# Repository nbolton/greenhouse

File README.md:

# Greenhouse
## An attempt to automate nature 🌶

### Prerequesits
- VSCode with Platform.io extension
- MinGW if Windows
  - [Chocolatey](https://chocolatey.org/): `choco install mingw`
  - Alternative: [MinGW](https://sourceforge.net/projects/mingwbuilds/files/latest/download)

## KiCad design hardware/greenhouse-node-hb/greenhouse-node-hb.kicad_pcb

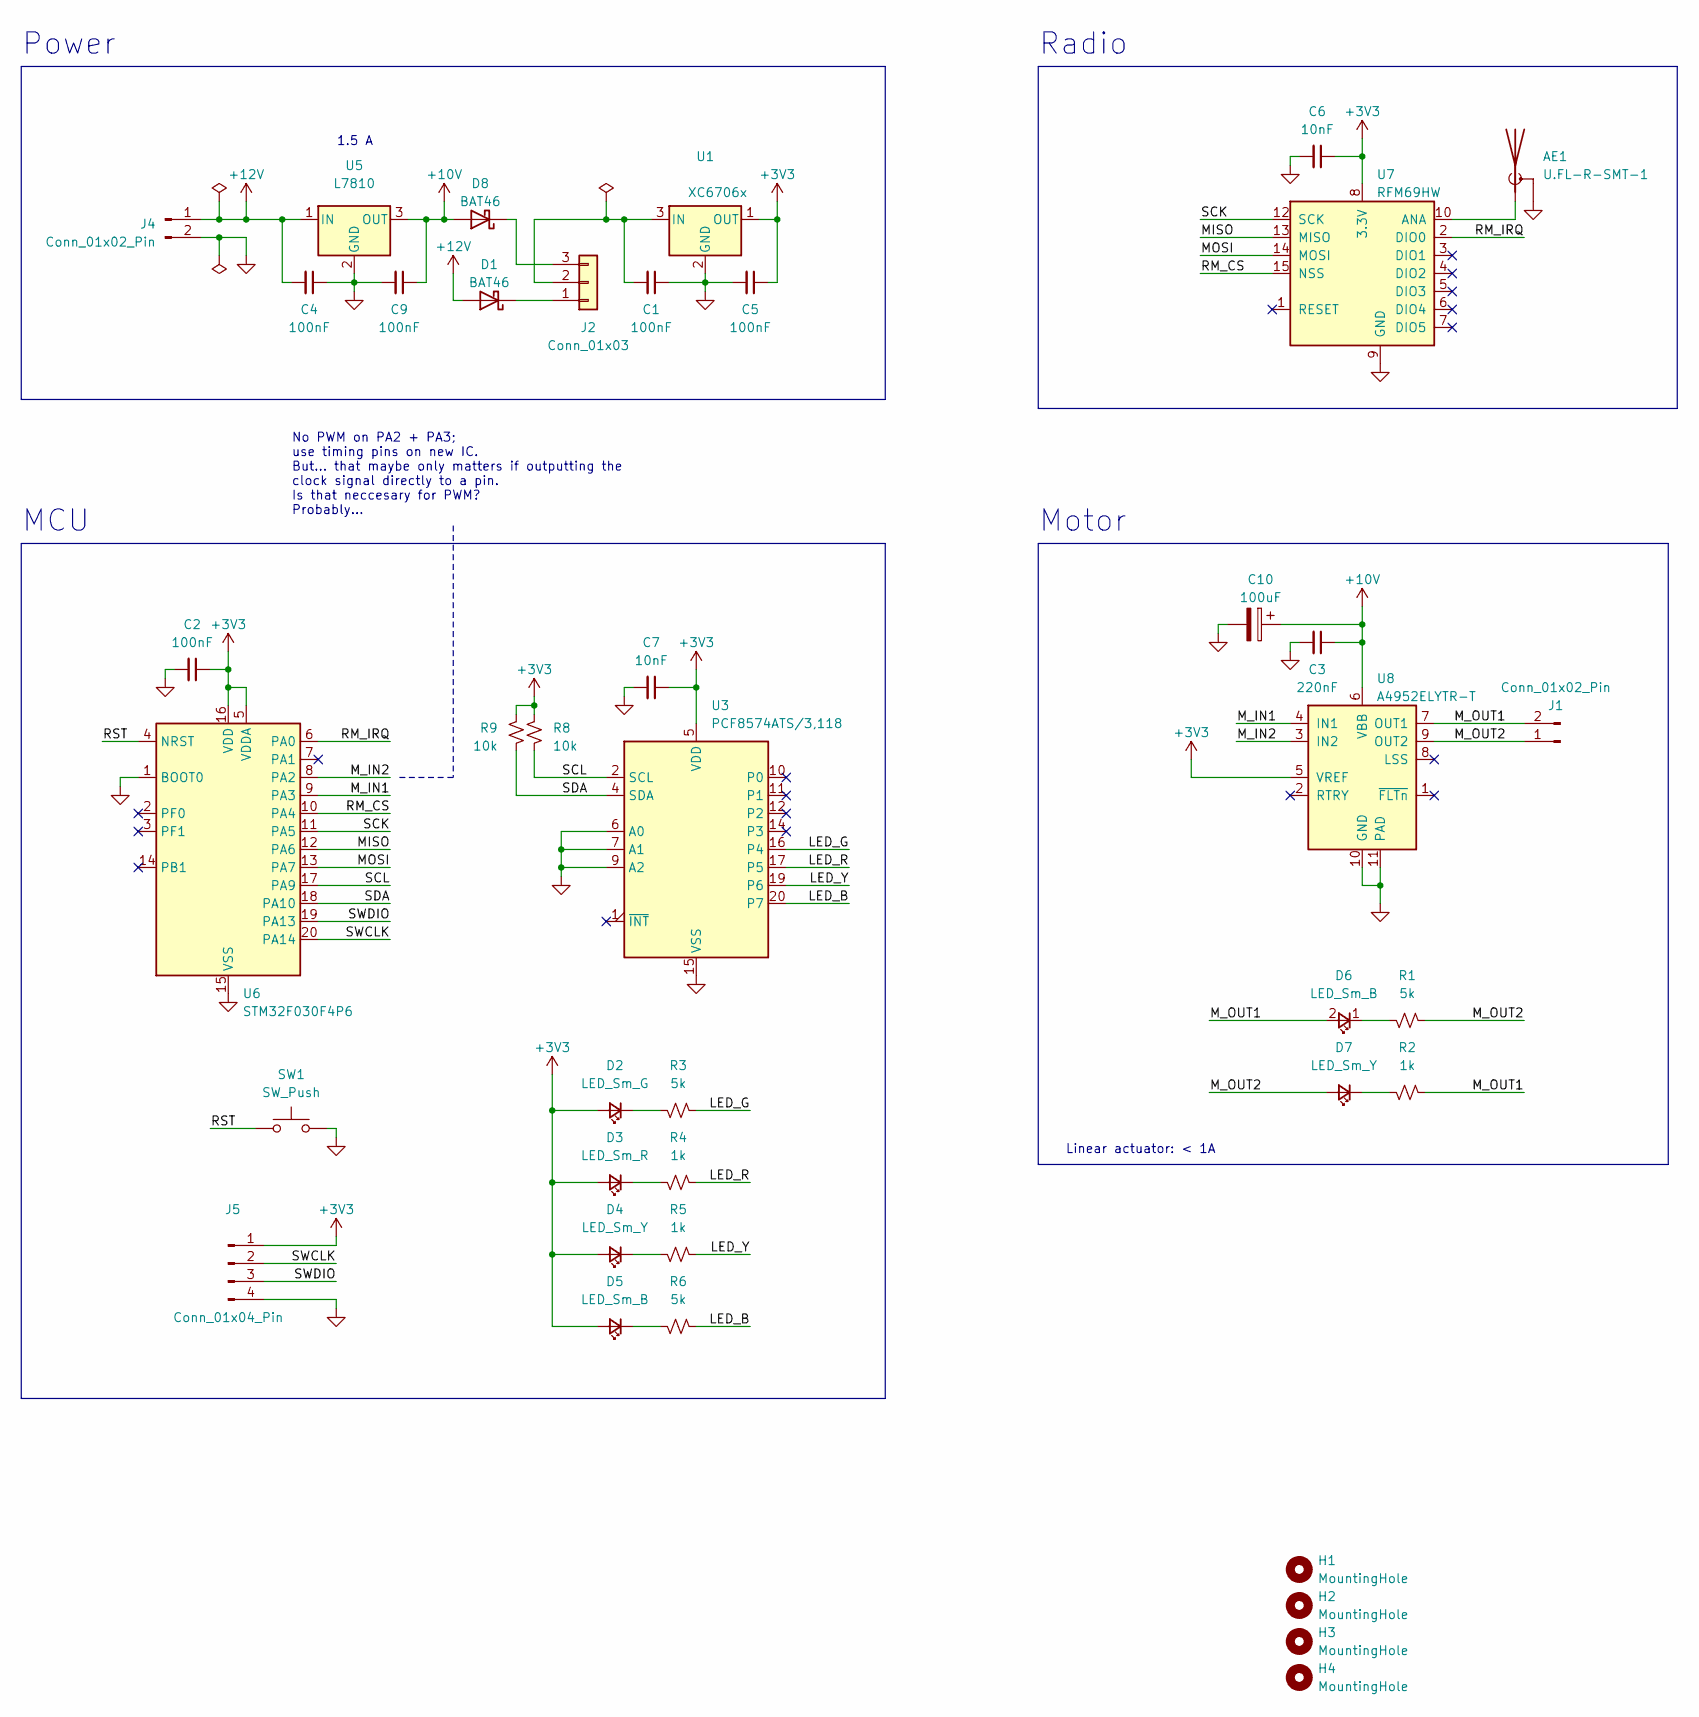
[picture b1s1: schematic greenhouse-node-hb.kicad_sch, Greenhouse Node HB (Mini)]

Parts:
AE1: U.FL-R-SMT-1; U.FL_Hirose_U.FL-R-SMT-1_Vertical
C1, C2, C4, C5, C9: 100nF; C_Disc_D4.7mm_W2.5mm_P5.00mm
C3: 220nF; C_Disc_D4.7mm_W2.5mm_P5.00mm
C6, C7: 10nF; C_Disc_D3.0mm_W2.0mm_P2.50mm
C10: 100uF; CP_Radial_D6.3mm_P2.50mm
D1, D8: BAT46; D_DO-35_SOD27_P7.62mm_Horizontal
D2: LED_Sm_G; LED_D3.0mm
D3: LED_Sm_R; LED_D3.0mm
D4, D7: LED_Sm_Y; LED_D3.0mm
D5, D6: LED_Sm_B; LED_D3.0mm
H1, H2, H3, H4: MountingHole; MountingHole_3.2mm_M3
J1, J4: Conn_01x02_Pin; Molex_KK-254_AE-6410-02A_1x02_P2.54mm_Vertical
J2: Conn_01x03; SolderJumper-3_P1.3mm_Bridged2Bar12_RoundedPad1.0x1.5mm
J5: Conn_01x04_Pin; JST_PH_B4B-PH-K_1x04_P2.00mm_Vertical
R1, R3, R6: 5k; R_Axial_DIN0207_L6.3mm_D2.5mm_P7.62mm_Horizontal
R2, R4, R5: 1k; R_Axial_DIN0207_L6.3mm_D2.5mm_P7.62mm_Horizontal
R8, R9: 10k; R_Axial_DIN0207_L6.3mm_D2.5mm_P7.62mm_Horizontal
SW1: SW_Push; SW_PUSH_6mm
U1: XC6706x; SOT-89-3
U3: PCF8574ATS/3,118; SSOP-20_4.4x6.5mm_P0.65mm
U5: L7810; TO-220-3_Horizontal_TabUp
U6: STM32F030F4P6; TSSOP-20_4.4x6.5mm_P0.65mm
U7: RFM69HW; HopeRF_RFM69HW
U8: A4952ELYTR-T; MSOP-10-1EP_3x3mm_P0.5mm_EP1.73x1.98mm

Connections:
+3V3: C2.1, C5.1, C6.1, C7.1, D2.2 (A), D3.2 (A), D4.2 (A), D5.2 (A), J5.1, R8.1, R9.1, U1.1 (OUT), U3.5 (VDD), U6.5 (VDDA), U6.16 (VDD), U7.8 (3.3V), U8.5 (VREF)
+10V: C3.1, C9.1, C10.1, D8.2 (A), U5.3 (OUT), U8.6 (VBB)
+12V: C4.2, D1.2 (A), J4.1, U5.1 (IN)
/LED_B: R6.1, U3.20 (P7)
/LED_G: R3.1, U3.16 (P4)
/LED_R: R4.1, U3.17 (P5)
/LED_Y: R5.1, U3.19 (P6)
/MISO: U6.12 (PA6), U7.13 (MISO)
/MOSI: U6.13 (PA7), U7.14 (MOSI)
/M_IN1: U6.9 (PA3), U8.4 (IN1)
/M_IN2: U6.8 (PA2), U8.3 (IN2)
/M_OUT1: D6.2 (A), J1.2, R2.1, U8.7 (OUT1)
/M_OUT2: D7.2 (A), J1.1, R1.1, U8.9 (OUT2)
/RM_CS: U6.10 (PA4), U7.15 (NSS)
/RM_IRQ: U6.6 (PA0), U7.2 (DIO0)
/RST: SW1.1, U6.4 (NRST)
/SCK: U6.11 (PA5), U7.12 (SCK)
/SCL: R8.2, U3.2 (SCL), U6.17 (PA9)
/SDA: R9.2, U3.4 (SDA), U6.18 (PA10)
/SWCLK: J5.2, U6.20 (PA14)
/SWDIO: J5.3, U6.19 (PA13)
GND: AE1.2 (Shield), C1.1, C2.2, C3.2, C4.1, C5.2, C6.2, C7.2, C9.2, C10.2, J4.2, J5.4, SW1.2, U1.2 (GND), U3.6 (A0), U3.7 (A1), U3.9 (A2), U3.15 (VSS), U5.2 (GND), U6.1 (BOOT0), U6.15 (VSS), U7.9 (GND), U7.11 (GND), U8.10 (GND), U8.11 (PAD)
unnamed: C1.2, J2.2, U1.3 (IN)
unnamed: AE1.1 (A), U7.10 (ANA)
unnamed: D1.1 (K), J2.1
unnamed: D2.1 (K), R3.2
unnamed: D3.1 (K), R4.2
unnamed: D4.1 (K), R5.2
unnamed: D5.1 (K), R6.2
unnamed: D6.1 (K), R1.2
unnamed: D7.1 (K), R2.2
unnamed: D8.1 (K), J2.3

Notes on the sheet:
Motor
MCU
Linear actuator: < 1A
Power
No PWM on PA2 + PA3; use timing pins on new IC. But... that maybe only matters if outputting the clock signal directly to a pin. Is that neccesary for PWM? Probably...
1.5 A
Radio

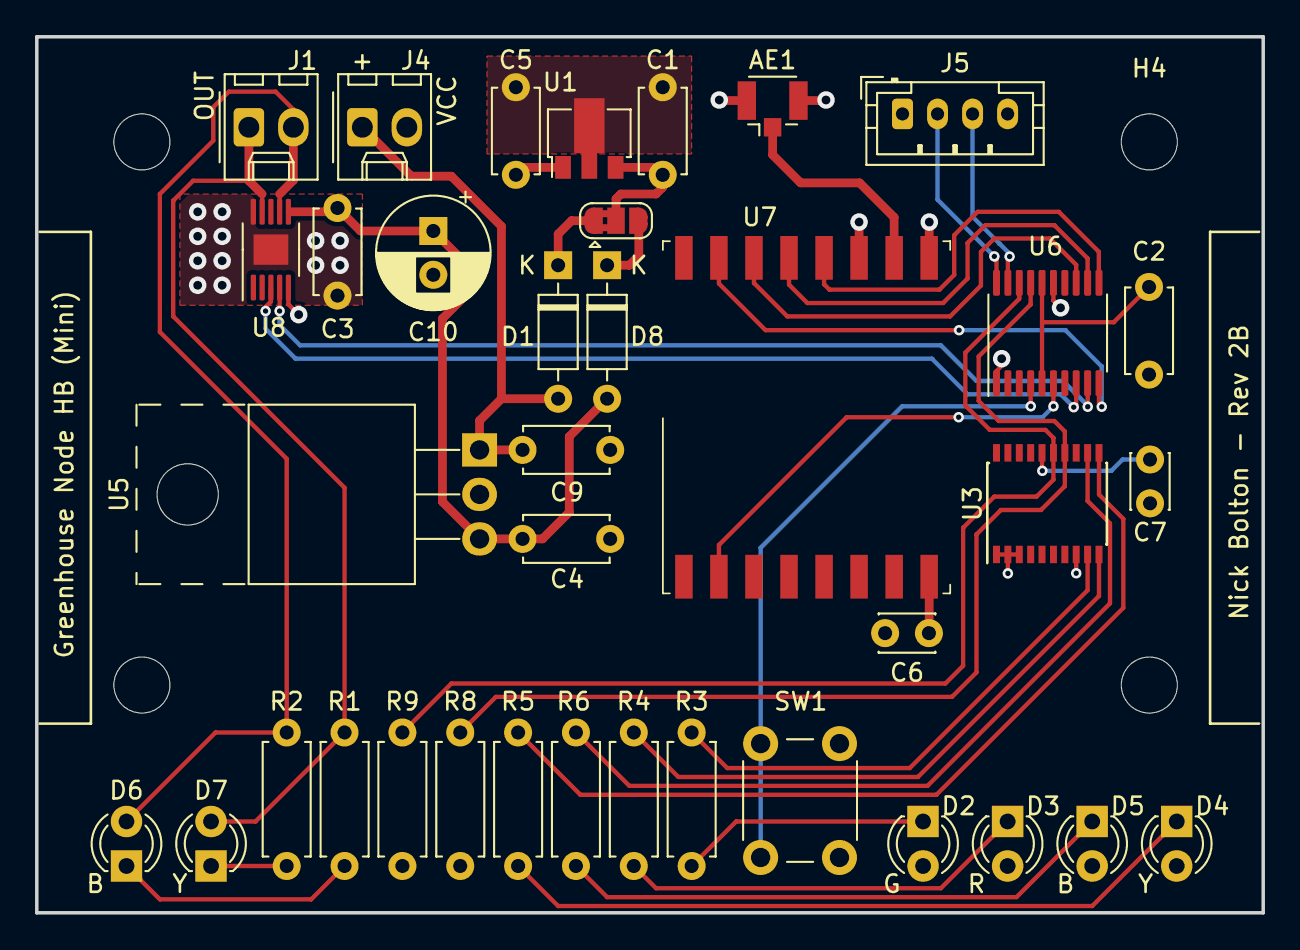
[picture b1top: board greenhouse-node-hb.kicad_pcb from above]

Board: 4 copper layers, 70.0 x 50.0 mm, 41 parts (0 on the bottom side), 32 nets.

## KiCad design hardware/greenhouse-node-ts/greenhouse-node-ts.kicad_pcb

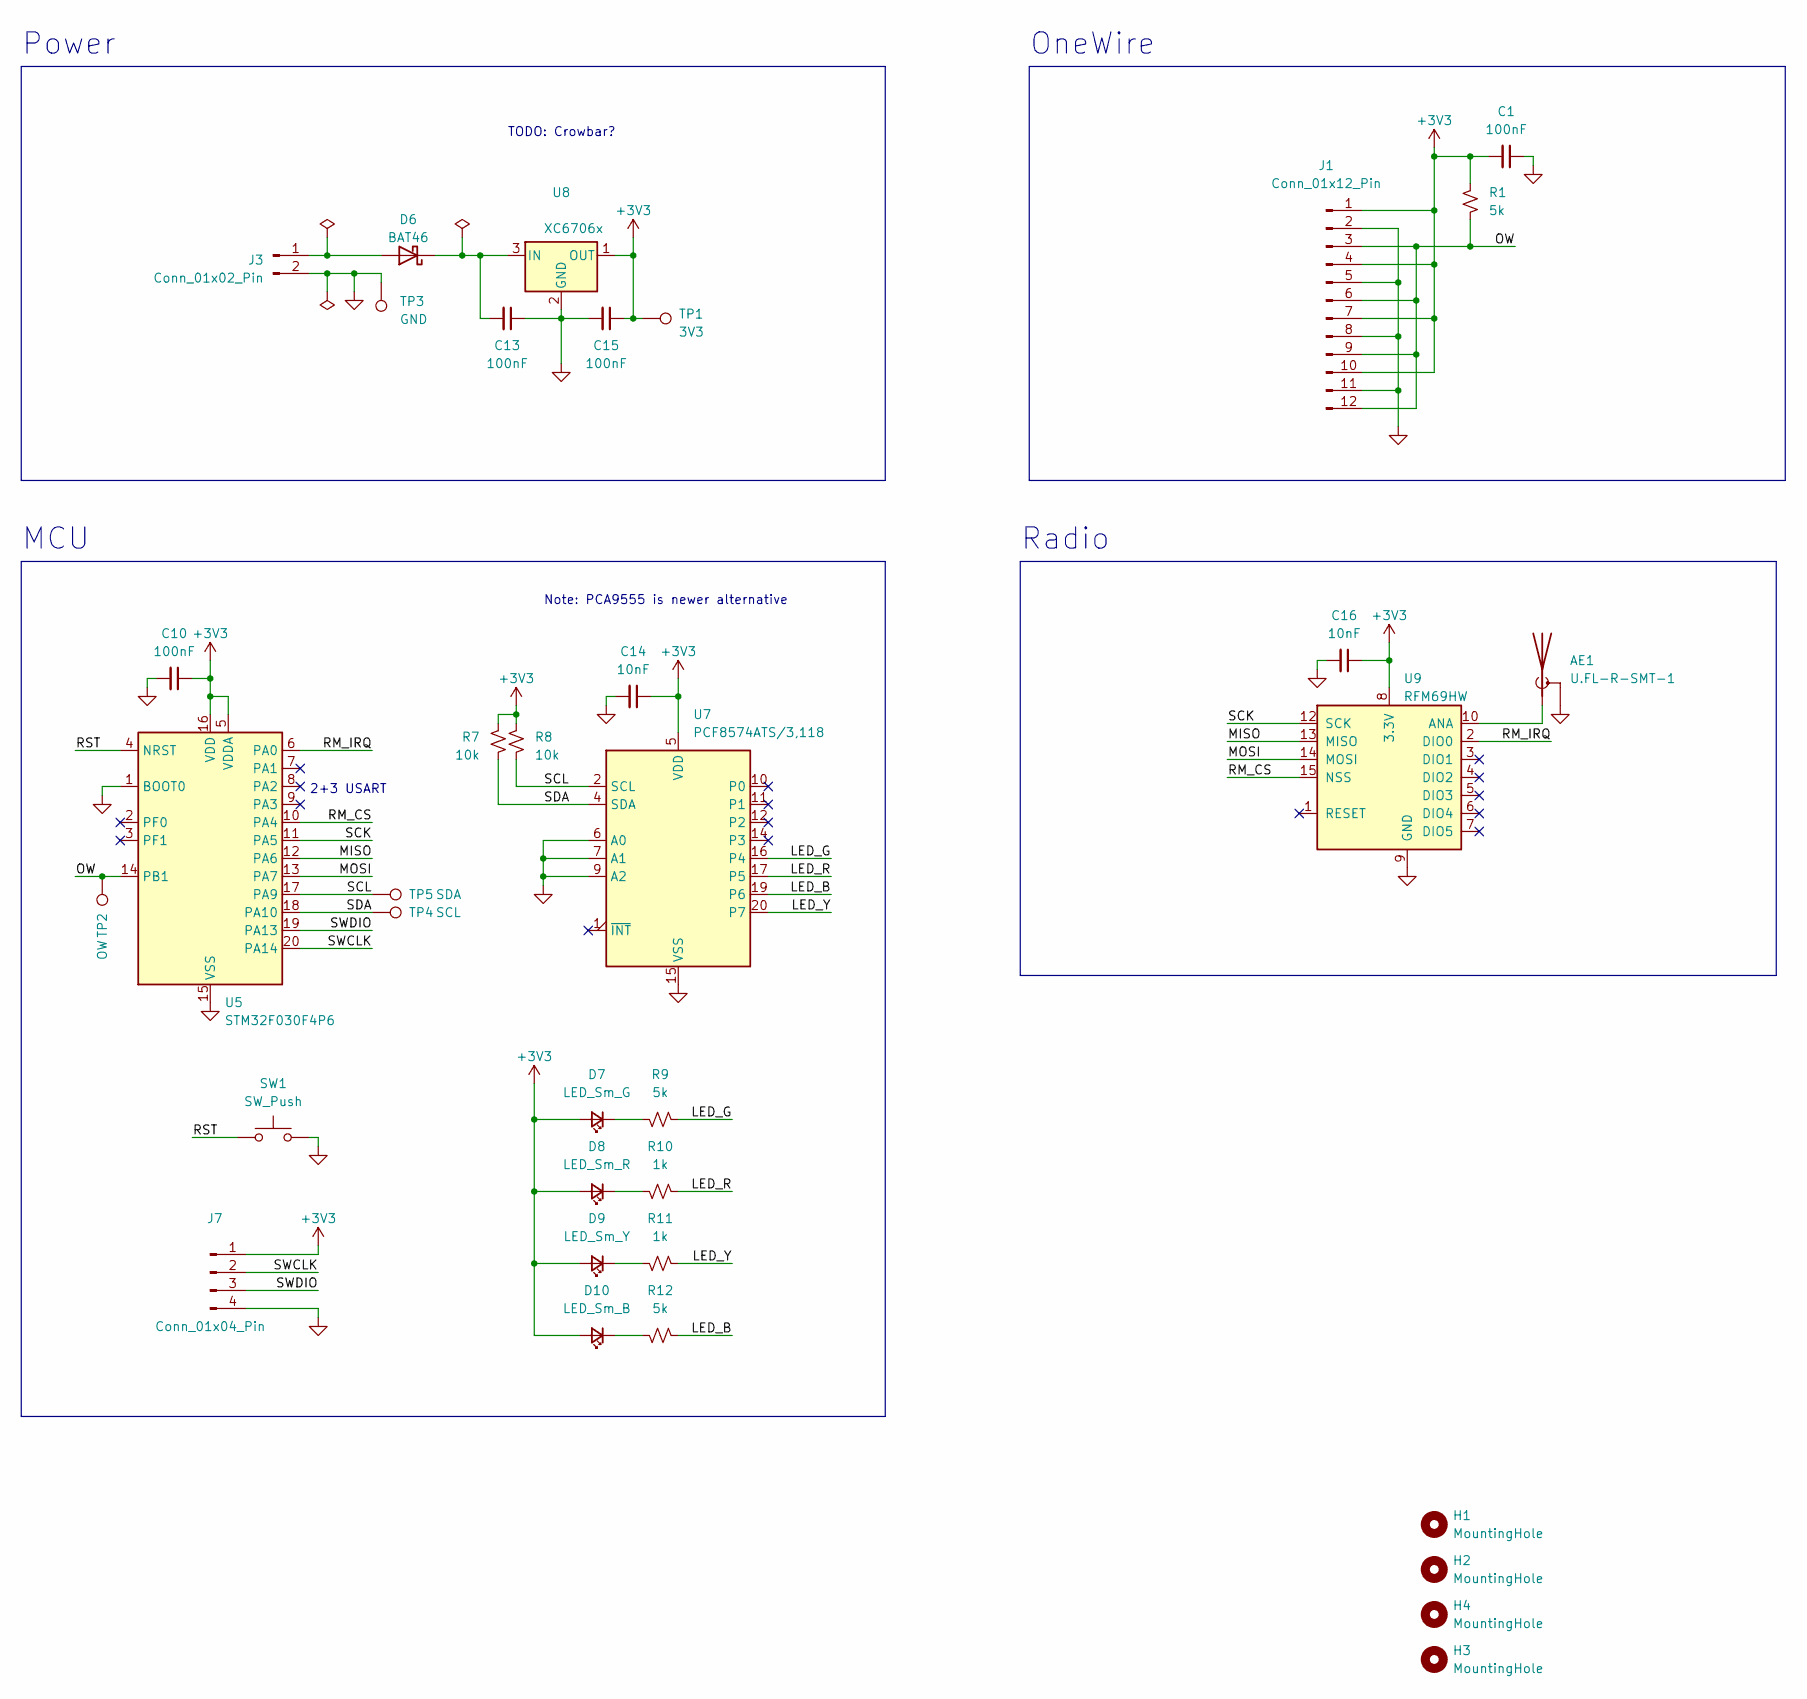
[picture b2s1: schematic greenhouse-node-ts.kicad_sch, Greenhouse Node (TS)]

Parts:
AE1: U.FL-R-SMT-1; U.FL_Hirose_U.FL-R-SMT-1_Vertical
C1, C10, C13, C15: 100nF; C_Disc_D4.7mm_W2.5mm_P5.00mm
C14, C16: 10nF; C_Disc_D3.0mm_W2.0mm_P2.50mm
D6: BAT46; D_DO-35_SOD27_P7.62mm_Horizontal
D7: LED_Sm_G; LED_D3.0mm
D8: LED_Sm_R; LED_D3.0mm
D9: LED_Sm_Y; LED_D3.0mm
D10: LED_Sm_B; LED_D3.0mm
H1, H2, H3, H4: MountingHole; MountingHole_3.2mm_M3
J1: Conn_01x12_Pin; JST_PH_B12B-PH-K_1x12_P2.00mm_Vertical
J3: Conn_01x02_Pin; Molex_KK-254_AE-6410-02A_1x02_P2.54mm_Vertical
J7: Conn_01x04_Pin; JST_PH_B4B-PH-K_1x04_P2.00mm_Vertical
R1, R9, R12: 5k; R_Axial_DIN0207_L6.3mm_D2.5mm_P7.62mm_Horizontal
R7, R8: 10k; R_Axial_DIN0207_L6.3mm_D2.5mm_P7.62mm_Horizontal
R10, R11: 1k; R_Axial_DIN0207_L6.3mm_D2.5mm_P7.62mm_Horizontal
SW1: SW_Push; SW_PUSH_6mm
TP1: 3V3; TestPoint_Keystone_5019_Minature
TP2: OW; TestPoint_Keystone_5019_Minature
TP3: GND; TestPoint_Keystone_5019_Minature
TP4: SCL; TestPoint_Keystone_5019_Minature
TP5: SDA; TestPoint_Keystone_5019_Minature
U5: STM32F030F4P6; TSSOP-20_4.4x6.5mm_P0.65mm
U7: PCF8574ATS/3,118; SSOP-20_4.4x6.5mm_P0.65mm
U8: XC6706x; SOT-89-3
U9: RFM69HW; HopeRF_RFM69HW

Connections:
+3V3: C1.2, C10.1, C14.1, C15.1, C16.1, D7.2 (A), D8.2 (A), D9.2 (A), D10.2 (A), J1.1, J1.4, J1.7, J1.10, J7.1, R1.1, R7.1, R8.1, TP1.1, U5.5 (VDDA), U5.16 (VDD), U7.5 (VDD), U8.1 (OUT), U9.8 (3.3V)
/LED_B: R12.1, U7.19 (P6)
/LED_G: R9.1, U7.16 (P4)
/LED_R: R10.1, U7.17 (P5)
/LED_Y: R11.1, U7.20 (P7)
/MISO: U5.12 (PA6), U9.13 (MISO)
/MOSI: U5.13 (PA7), U9.14 (MOSI)
/OW: J1.3, J1.6, J1.9, J1.12, R1.2, TP2.1, U5.14 (PB1)
/RM_CS: U5.10 (PA4), U9.15 (NSS)
/RM_IRQ: U5.6 (PA0), U9.2 (DIO0)
/RST: SW1.1, U5.4 (NRST)
/SCK: U5.11 (PA5), U9.12 (SCK)
/SCL: R8.2, TP5.1, U5.17 (PA9), U7.2 (SCL)
/SDA: R7.2, TP4.1, U5.18 (PA10), U7.4 (SDA)
/SWCLK: J7.2, U5.20 (PA14)
/SWDIO: J7.3, U5.19 (PA13)
GND: AE1.2 (Shield), C1.1, C10.2, C13.1, C14.2, C15.2, C16.2, J1.2, J1.5, J1.8, J1.11, J3.2, J7.4, SW1.2, TP3.1, U5.1 (BOOT0), U5.15 (VSS), U7.6 (A0), U7.7 (A1), U7.9 (A2), U7.15 (VSS), U8.2 (GND), U9.9 (GND), U9.11 (GND)
unnamed: AE1.1 (A), U9.10 (ANA)
unnamed: D6.2 (A), J3.1
unnamed: C13.2, D6.1 (K), U8.3 (IN)
unnamed: D7.1 (K), R9.2
unnamed: D8.1 (K), R10.2
unnamed: D9.1 (K), R11.2
unnamed: D10.1 (K), R12.2

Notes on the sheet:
Note: PCA9555 is newer alternative
Power
MCU
OneWire
Radio
TODO: Crowbar?
2+3 USART

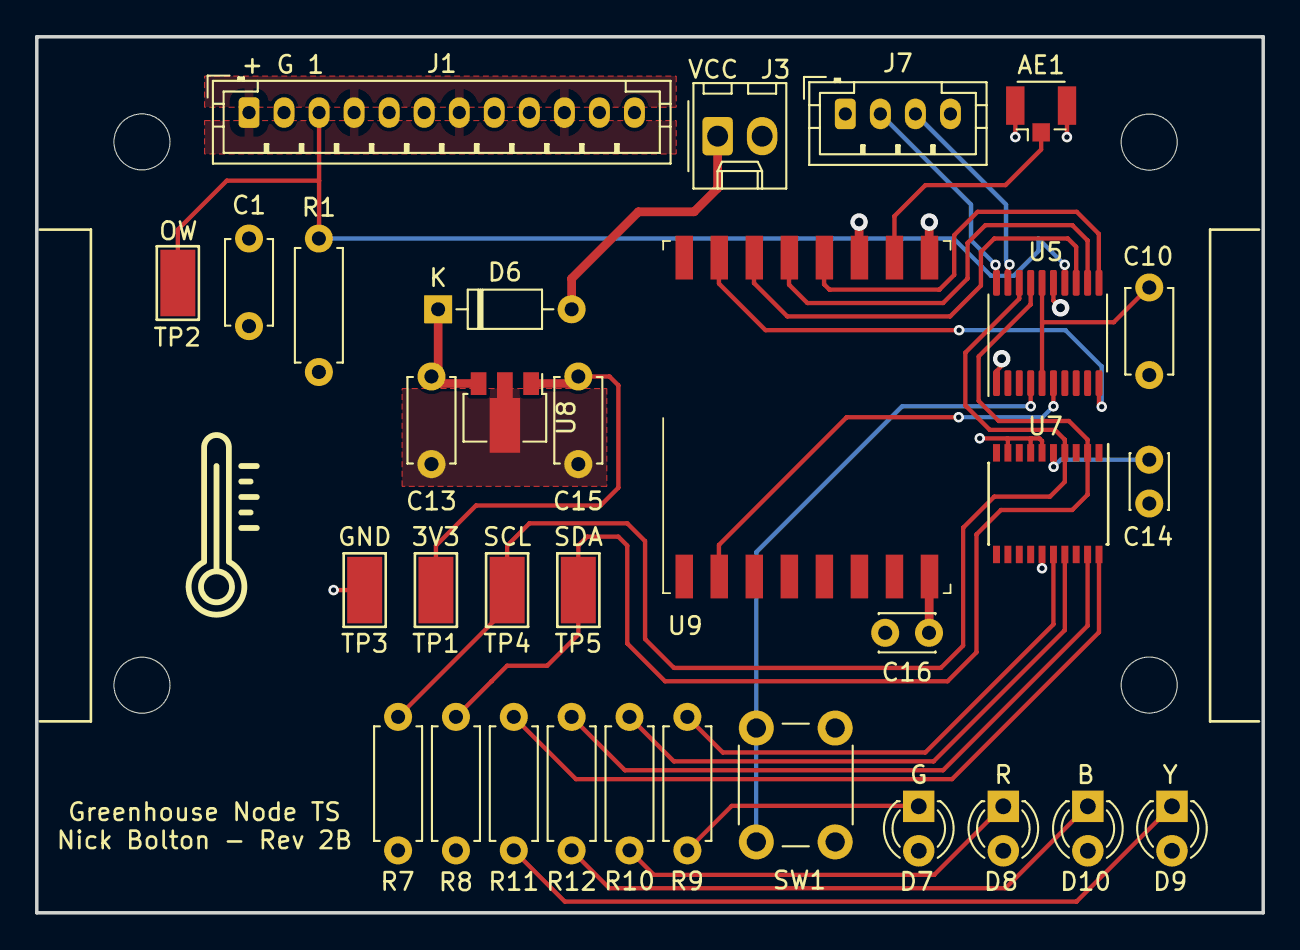
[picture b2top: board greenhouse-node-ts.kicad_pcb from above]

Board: 4 copper layers, 70.0 x 50.0 mm, 36 parts (0 on the bottom side), 24 nets.

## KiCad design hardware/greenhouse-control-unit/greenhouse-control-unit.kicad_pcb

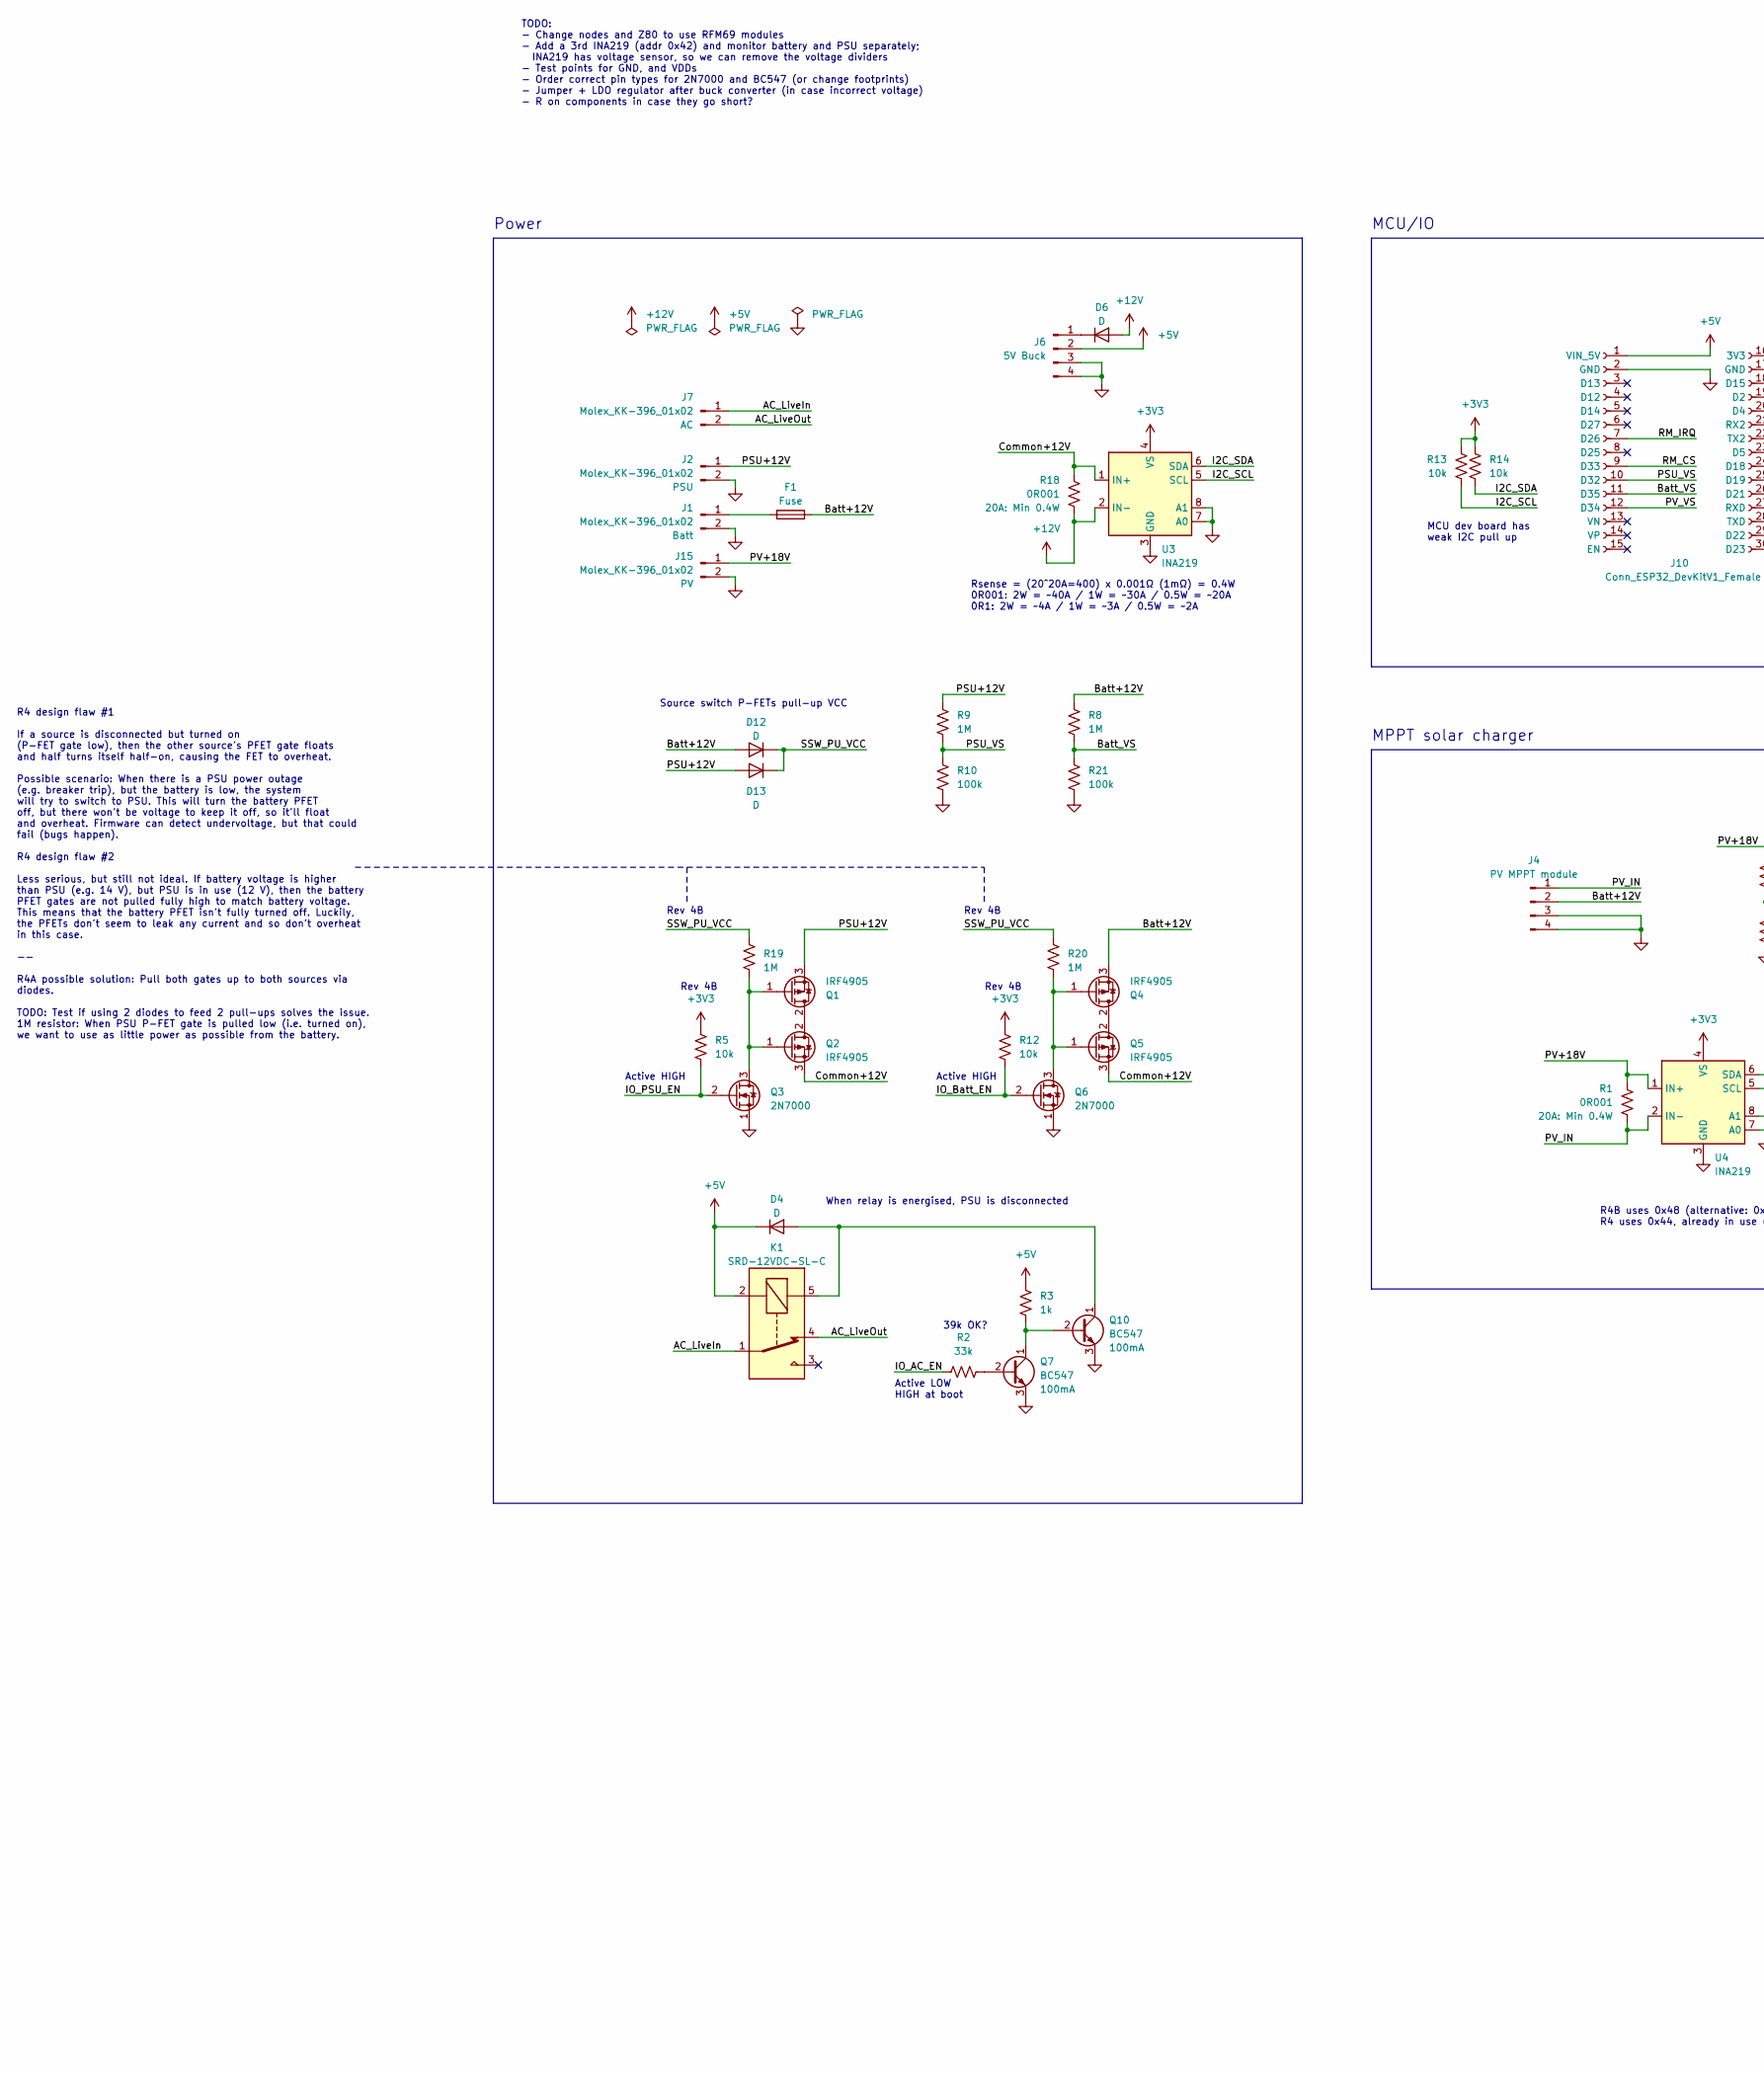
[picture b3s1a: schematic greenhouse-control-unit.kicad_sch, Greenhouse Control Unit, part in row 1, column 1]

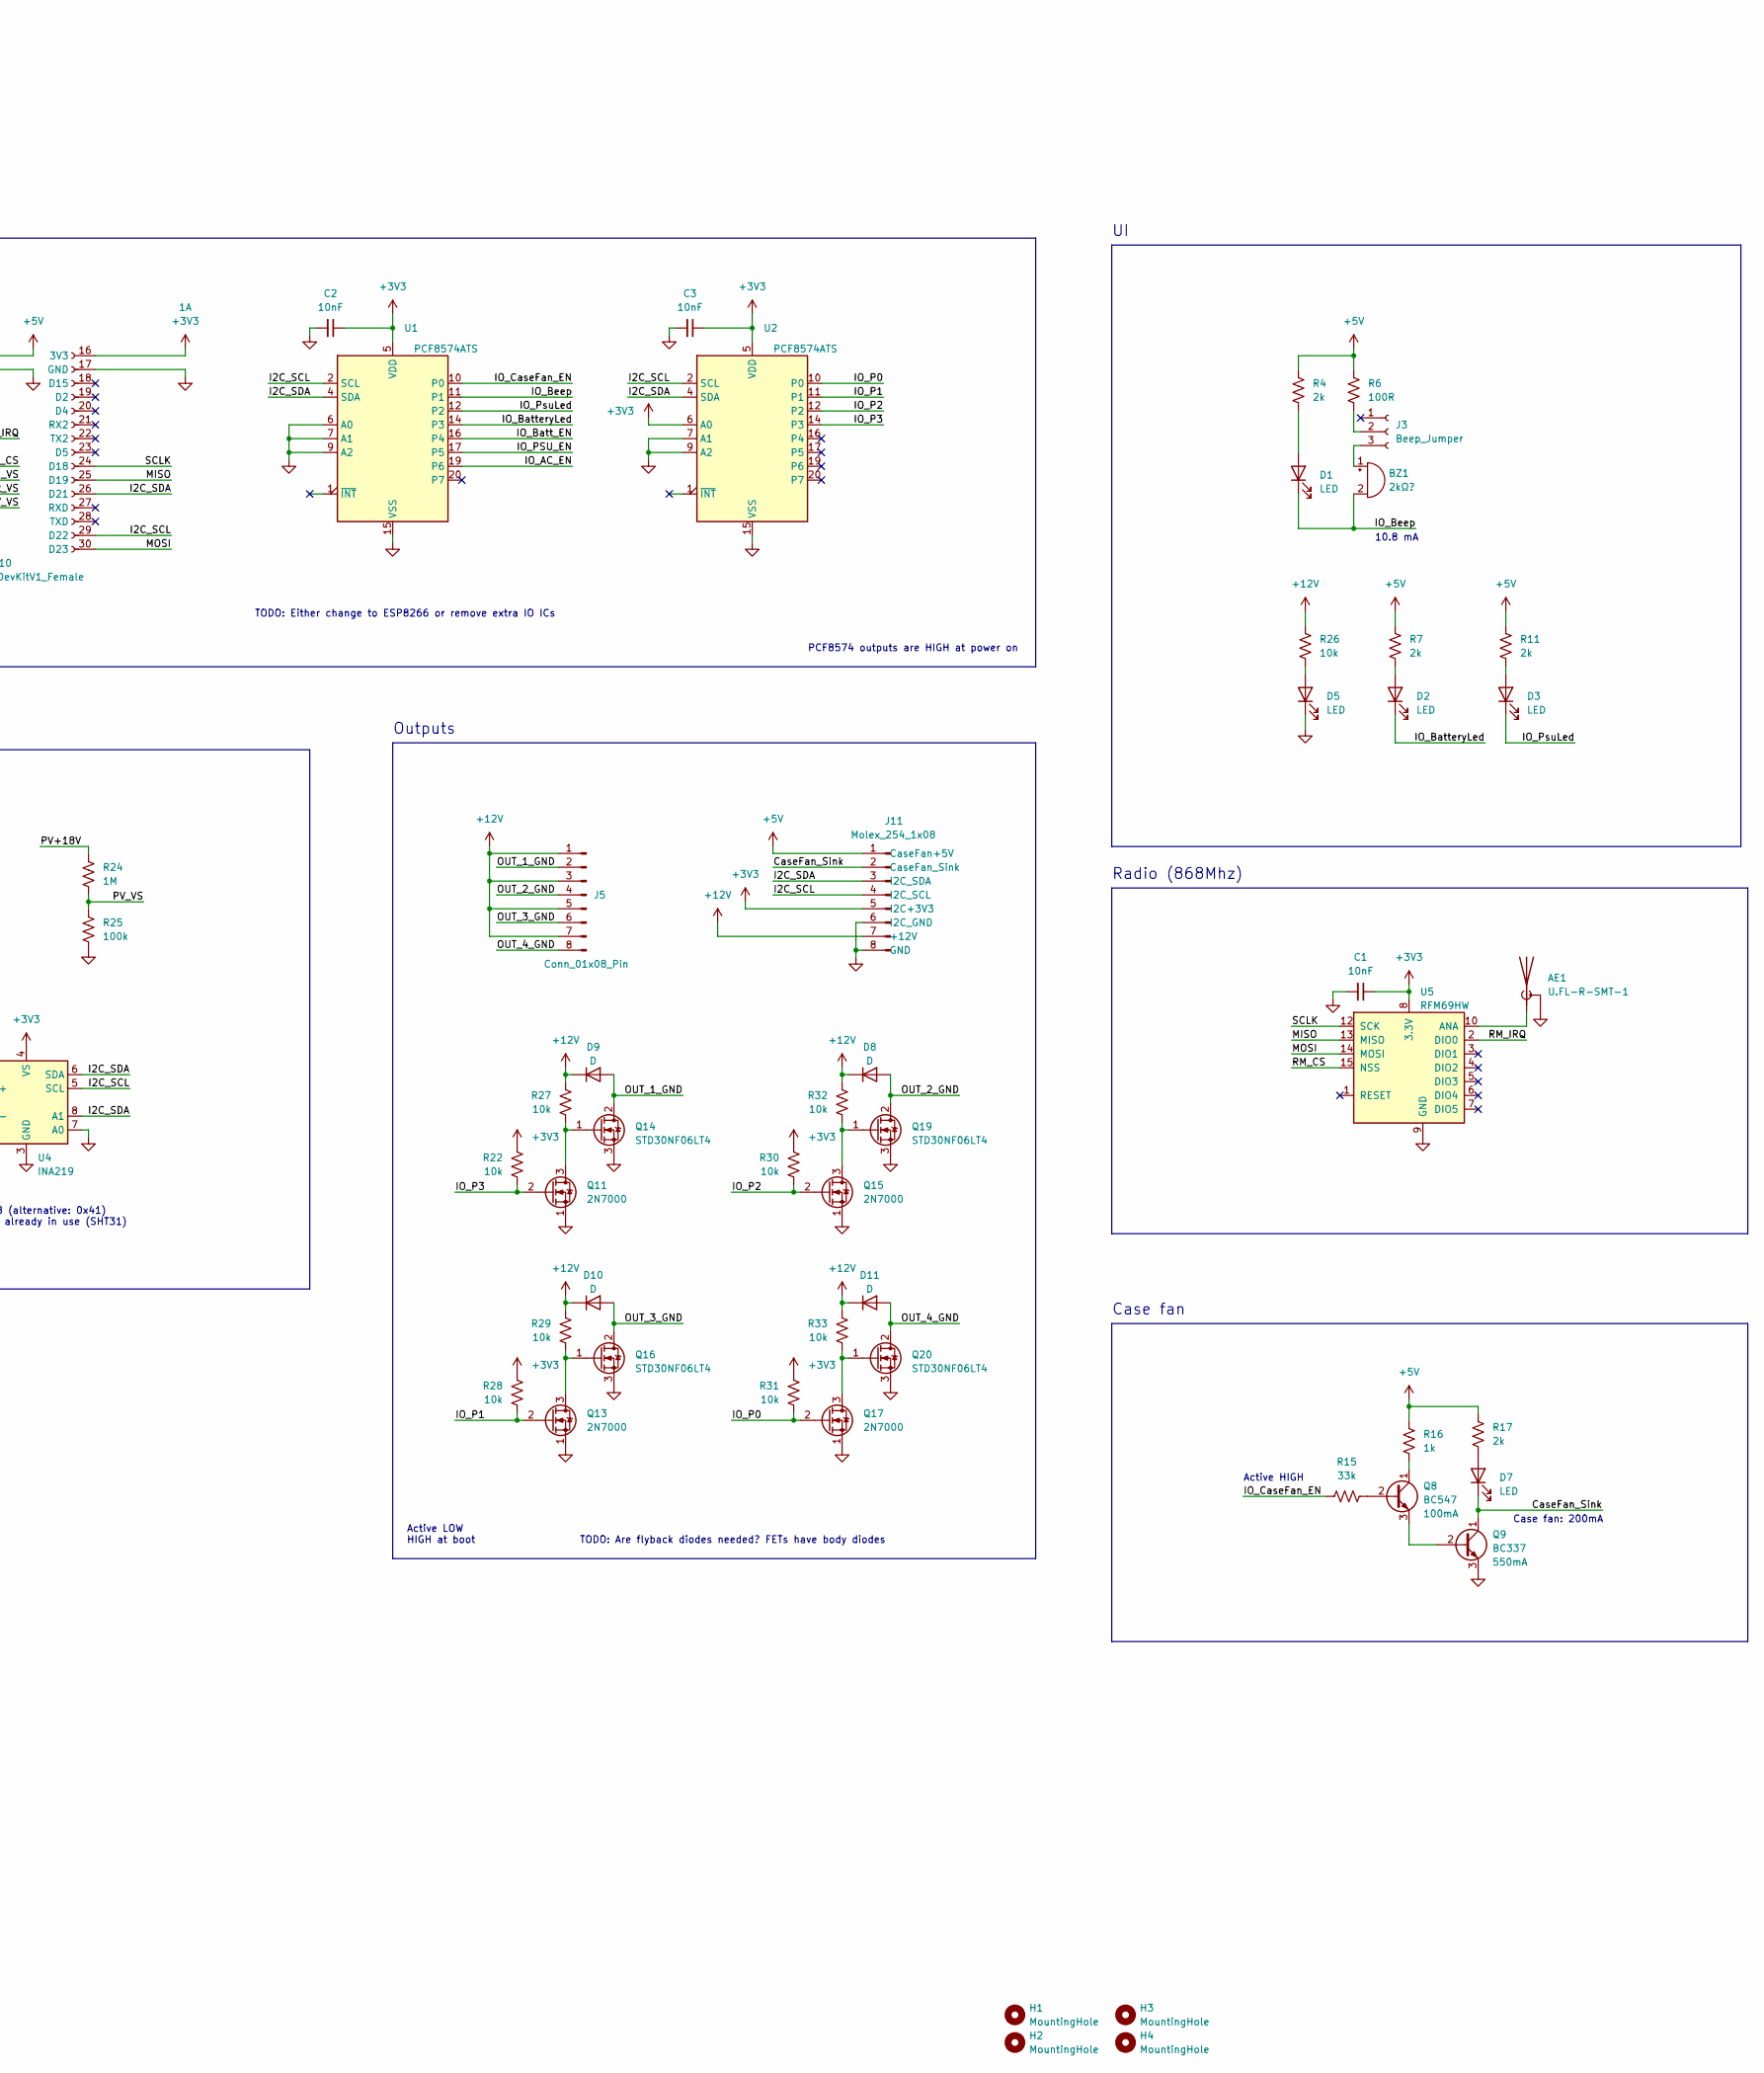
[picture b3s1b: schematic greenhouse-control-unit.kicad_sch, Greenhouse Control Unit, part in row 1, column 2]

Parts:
AE1: U.FL-R-SMT-1; U.FL_Hirose_U.FL-R-SMT-1_Vertical
BZ1: 2kΩ?; Buzzer_12x9.5RM7.6
C1, C2, C3: 10nF; C_Disc_D3.0mm_W2.0mm_P2.50mm
D1, D2, D3, D5, D7: LED; LED_D5.0mm
D4, D12, D13: D; D_DO-35_SOD27_P7.62mm_Horizontal
D6: D; D_DO-41_SOD81_P7.62mm_Horizontal
D8, D9, D10, D11: D; D_DO-41_SOD81_P2.54mm_Vertical_AnodeUp
F1: Fuse; Fuse_3522-2_L
H1, H2, H3, H4: MountingHole; MountingHole_3mm
J1, J2, J7, J15: Molex_KK-396_01x02; Molex_KK-396_1x02_P3.96mm_Vertical
J3: Beep_Jumper; PinHeader_1x03_P2.54mm_Vertical
J4: PV MPPT module; MPPT-10A-Module
J5: Conn_01x08_Pin; Molex_KK-396_1x08_P3.96mm_Vertical
J6: 5V Buck; Buck_Module
J10: Conn_ESP32_DevKitV1_Female; PinSocket_ESP32_DevKitV1
J11: Molex_254_1x08; Molex_KK-254_AE-6410-08A_1x08_P2.54mm_Vertical
K1: SRD-12VDC-SL-C; Relay_SRD-12VDC-SL-C
Q1, Q2, Q4, Q5: IRF4905; TO-220-3_Vertical
Q3, Q6, Q11, Q13, Q15, Q17: 2N7000; TO-92_Inline
Q7, Q8, Q10: BC547; TO-92_Inline
Q9: BC337; TO-92_Inline
Q14, Q16, Q19, Q20: STD30NF06LT4; TO-252-2
R1, R18: 0R001; R_2512_6332Metric_Pad1.40x3.35mm_HandSolder
R2, R15: 33k; R_Axial_DIN0207_L6.3mm_D2.5mm_P7.62mm_Horizontal
R3, R16: 1k; R_Axial_DIN0207_L6.3mm_D2.5mm_P7.62mm_Horizontal
R4, R7, R11, R17: 2k; R_Axial_DIN0207_L6.3mm_D2.5mm_P7.62mm_Horizontal
R5, R12, R22, R26, R27, R28, R29, R30, R31, R32, R33: 10k; R_Axial_DIN0207_L6.3mm_D2.5mm_P7.62mm_Horizontal
R6: 100R; R_Axial_DIN0207_L6.3mm_D2.5mm_P7.62mm_Horizontal
R8, R9, R19, R20, R24: 1M; R_Axial_DIN0207_L6.3mm_D2.5mm_P7.62mm_Horizontal
R10, R21, R25: 100k; R_Axial_DIN0207_L6.3mm_D2.5mm_P7.62mm_Horizontal
R13, R14: 10k; R_Axial_DIN0204_L3.6mm_D1.6mm_P5.08mm_Horizontal
U1, U2: PCF8574ATS; SSOP-20_4.4x6.5mm_P0.65mm
U3, U4: INA219; SOT-23-8
U5: RFM69HW; HopeRF_RFM69HW

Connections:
+3V3: C1.1, C2.1, C3.1, J10.16 (3V3), J11.5 (I2C+3V3), R5.2, R12.2, R13.1, R14.1, R22.1, R28.1, R30.1, R31.1, U1.5 (VDD), U2.5 (VDD), U2.6 (A0), U3.4 (VS), U4.4 (VS), U5.8 (3.3V)
+5V: D4.1 (K), J6.2, J10.1 (VIN_5V), J11.1 (CaseFan+5V), K1.2, R3.2, R4.1, R6.1, R7.1, R11.1, R16.2, R17.1
+12V: D6.2 (A), D8.1 (K), D9.1 (K), D10.1 (K), D11.1 (K), J5.1, J5.3, J5.5, J5.7, J11.7 (+12V), R18.1, R26.1, R27.1, R29.1, R32.1, R33.1, U3.2 (IN-)
/AC_LiveIn: J7.1, K1.1
/AC_LiveOut: J7.2, K1.4
/Batt+12V: D12.2 (A), F1.1, J4.2, Q4.3 (S), R8.1
/Batt_VS: J10.11 (D35), R8.2, R21.1
/CaseFan_Sink: D7.1 (K), J11.2 (CaseFan_Sink), Q9.1 (C)
/Common+12V: Q2.3 (S), Q5.3 (S), R18.2, U3.1 (IN+)
/I2C_SCL: J10.29 (D22), J11.4 (I2C_SCL), R13.2, U1.2 (SCL), U2.2 (SCL), U3.5 (SCL), U4.5 (SCL)
/I2C_SDA: J10.26 (D21), J11.3 (I2C_SDA), R14.2, U1.4 (SDA), U2.4 (SDA), U3.6 (SDA), U4.6 (SDA), U4.8 (A1)
/IO_AC_EN: R2.1, U1.19 (P6)
/IO_Batt_EN: Q6.2 (G), R12.1, U1.16 (P4)
/IO_BatteryLed: D2.1 (K), U1.14 (P3)
/IO_Beep: BZ1.2 (+), D1.1 (K), U1.11 (P1)
/IO_CaseFan_EN: R15.1, U1.10 (P0)
/IO_P0: Q17.2 (G), R31.2, U2.10 (P0)
/IO_P1: Q13.2 (G), R28.2, U2.11 (P1)
/IO_P2: Q15.2 (G), R30.2, U2.12 (P2)
/IO_P3: Q11.2 (G), R22.2, U2.14 (P3)
/IO_PSU_EN: Q3.2 (G), R5.1, U1.17 (P5)
/IO_PsuLed: D3.1 (K), U1.12 (P2)
/MISO: J10.25 (D19), U5.13 (MISO)
/MOSI: J10.30 (D23), U5.14 (MOSI)
/OUT_1_GND: D9.2 (A), J5.2, Q14.2 (D)
/OUT_2_GND: D8.2 (A), J5.4, Q19.2 (D)
/OUT_3_GND: D10.2 (A), J5.6, Q16.2 (D)
/OUT_4_GND: D11.2 (A), J5.8, Q20.2 (D)
/PSU+12V: D13.2 (A), J2.1, Q1.3 (S), R9.1
/PSU_VS: J10.10 (D32), R9.2, R10.1
/PV+18V: J15.1, R1.2, R24.1, U4.1 (IN+)
/PV_IN: J4.1, R1.1, U4.2 (IN-)
/PV_VS: J10.12 (D34), R24.2, R25.1
/RM_CS: J10.9 (D33), U5.15 (NSS)
/RM_IRQ: J10.7 (D26), U5.2 (DIO0)
/SCLK: J10.24 (D18), U5.12 (SCK)
/SSW_PU_VCC: D12.1 (K), D13.1 (K), R19.2, R20.2
GND: AE1.2 (Shield), C1.2, C2.2, C3.2, D5.1 (K), J1.2, J2.2, J4.3, J4.4, J6.3, J6.4, J10.2 (GND), J10.17 (GND), J11.6 (I2C_GND), J11.8 (GND), J15.2, Q3.1 (S), Q6.1 (S), Q7.3 (E), Q9.3 (E), Q10.3 (E), Q11.1 (S), Q13.1 (S), Q14.3 (S), Q15.1 (S), Q16.3 (S), Q17.1 (S), Q19.3 (S), Q20.3 (S), R10.2, R21.2, R25.2, U1.6 (A0), U1.7 (A1), U1.9 (A2), U1.15 (VSS), U2.7 (A1), U2.9 (A2), U2.15 (VSS), U3.3 (GND), U3.7 (A0), U3.8 (A1), U4.3 (GND), U4.7 (A0), U5.9 (GND), U5.11 (GND)
unnamed: AE1.1 (A), U5.10 (ANA)
unnamed: BZ1.1 (-), J3.3
unnamed: D1.2 (A), R4.2
unnamed: D2.2 (A), R7.2
unnamed: D3.2 (A), R11.2
unnamed: D4.2 (A), K1.5, Q10.1 (C)
unnamed: D5.2 (A), R26.2
unnamed: D6.1 (K), J6.1
unnamed: D7.2 (A), R17.2
unnamed: F1.2, J1.1
unnamed: J3.2, R6.2
unnamed: Q1.2 (D), Q2.2 (D)
unnamed: Q1.1 (G), Q2.1 (G), Q3.3 (D), R19.1
unnamed: Q4.2 (D), Q5.2 (D)
unnamed: Q4.1 (G), Q5.1 (G), Q6.3 (D), R20.1
unnamed: Q7.2 (B), R2.2
unnamed: Q8.2 (B), R15.2
unnamed: Q8.1 (C), R16.1
unnamed: Q8.3 (E), Q9.2 (B)
unnamed: Q7.1 (C), Q10.2 (B), R3.1
unnamed: Q11.3 (D), Q14.1 (G), R27.2
unnamed: Q13.3 (D), Q16.1 (G), R29.2
unnamed: Q15.3 (D), Q19.1 (G), R32.2
unnamed: Q17.3 (D), Q20.1 (G), R33.2

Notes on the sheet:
Source switch P-FETs pull-up VCC
When relay is energised, PSU is disconnected
R4B uses 0x48 (alternative: 0x41) R4 uses 0x44, already in use (SHT31)
Rsense = (20^20A=400) x 0.001Ω (1mΩ) = 0.4W 0R001: 2W = ~40A / 1W = ~30A / 0.5W = ~20A 0R1: 2W = ~4A / 1W = ~3A / 0.5W = ~2A
R4 design flaw #1 If a source is disconnected but turned on (P-FET gate low), then the other source's PFET gate floats and half turns itself half-on, causing the FET to overheat. Possible scenario: When there is a PSU power outage (e.g. breaker trip), but the battery is low, the system will try to 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
TODO: - Change nodes and Z80 to use RFM69 modules - Add a 3rd INA219 (addr 0x42) and monitor battery and PSU separately; INA219 has voltage sensor, so we can remove the voltage dividers - Test points for GND, and VDDs - Order correct pin types for 2N7000 and BC547 (or change footprints) - Jumper + 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
Rev 4B
MCU/IO
TODO: Either change to ESP8266 or remove extra IO ICs
Active HIGH
Active LOW HIGH at boot
Case fan: 200mA
Power
Radio (868Mhz)
Outputs
10.8 mA
MCU dev board has weak I2C pull up
TODO: Are flyback diodes needed? FETs have body diodes
PCF8574 outputs are HIGH at power on
39k OK?
Case fan
MPPT solar charger
